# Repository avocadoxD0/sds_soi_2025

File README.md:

# Reaction Wheel Attitude Control System

This repository contains the complete design and development of a single-axis reaction wheel system for satellite attitude stabilization. The project brings together mechanical modeling, circuit design, and embedded control to achieve angular velocity detumbling.

The system is built around a reaction wheel mechanism, controlled using real-time feedback from an onboard IMU. All major subsystems including mechanical structure, electronics, and control algorithm are developed in coordination to function as a unified, self-contained system.

This repository serves as a consolidated record of the entire design process, including CAD models, PCB design files, and control code.

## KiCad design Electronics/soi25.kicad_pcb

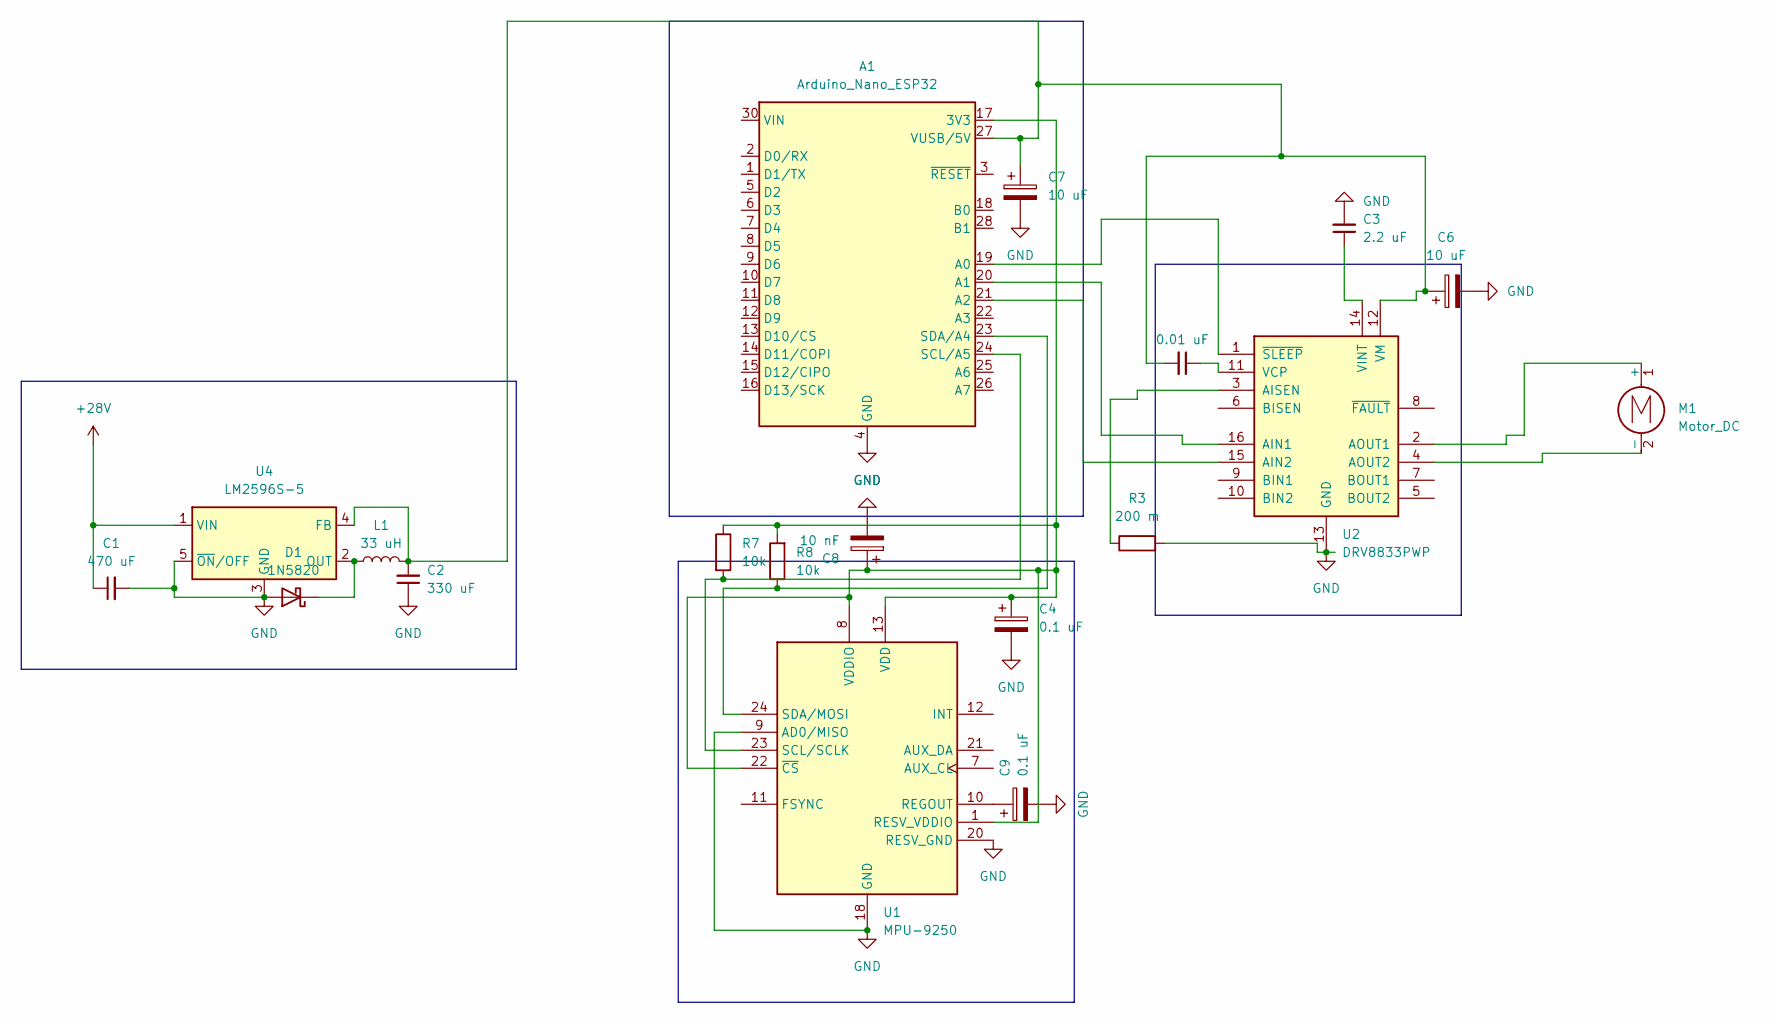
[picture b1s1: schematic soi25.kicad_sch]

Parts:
A1: Arduino_Nano_ESP32; Arduino_Nano
C1: 470 uF; C_Radial_D4.0mm_H5.0mm_P1.50mm
C2: 330 uF; C_Radial_D4.0mm_H5.0mm_P1.50mm
C3: 2.2 uF; C_0402_1005Metric_Pad0.74x0.62mm_HandSolder
C4, C9: 0.1 uF; C_0402_1005Metric_Pad0.74x0.62mm_HandSolder
C5: 0.01 uF; C_0402_1005Metric_Pad0.74x0.62mm_HandSolder
C6, C7: 10 uF; C_0402_1005Metric_Pad0.74x0.62mm_HandSolder
C8: 10 nF; C_0402_1005Metric_Pad0.74x0.62mm_HandSolder
D1: 1N5820; D_0201_0603Metric
L1: 33 uH; L_Wurth_WE-LQSH-2010
M1: Motor_DC; Vybronics_VZ30C1T8219732L
R3: 200 m; R_0402_1005Metric_Pad0.72x0.64mm_HandSolder
R7, R8: 10k; R_0402_1005Metric_Pad0.72x0.64mm_HandSolder
U1: MPU-9250; InvenSense_QFN-24_3x3mm_P0.4mm
U2: DRV8833PWP; HTSSOP-16-1EP_4.4x5mm_P0.65mm_EP3.4x5mm_Mask2.46x2.31mm_The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
U4: LM2596S-5; TO-263-5_TabPin3

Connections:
+28V: C1.1, U4.1 (VIN)
GND: A1.4 (GND), A1.29 (GND), C1.2, C2.1, C3.2, C4.2, C6.2, C7.2, C8.2, C9.2, D1.2 (A), R3.2, U1.9 (AD0/MISO), U1.18 (GND), U1.20 (RESV_GND), U2.13 (GND), U2.17 (GND), U4.3 (GND), U4.5 (~ON/OFF)
unnamed: A1.17 (3V3), C4.1, C8.1, R7.1, R8.2, U1.1 (RESV_VDDIO), U1.8 (VDDIO), U1.13 (VDD), U1.22 (~CS)
unnamed: A1.19 (A0), U2.1 (~SLEEP)
unnamed: A1.20 (A1), U2.16 (AIN1)
unnamed: A1.21 (A2), U2.15 (AIN2)
unnamed: A1.24 (SCL/A5), R7.2, U1.23 (SCL/SCLK)
unnamed: A1.23 (SDA/A4), R8.1, U1.24 (SDA/MOSI)
unnamed: A1.27 (VUSB/5V), C2.2, C5.2, C6.1, C7.1, L1.2, U2.12 (VM), U4.4 (FB)
unnamed: D1.1 (K), L1.1, U4.2 (OUT)
unnamed: M1.1 (+), U2.2 (AOUT1)
unnamed: M1.2 (-), U2.4 (AOUT2)
unnamed: C9.1, U1.10 (REGOUT)
unnamed: R3.1, U2.3 (AISEN)
unnamed: C5.1, U2.11 (VCP)
unnamed: C3.1, U2.14 (VINT)

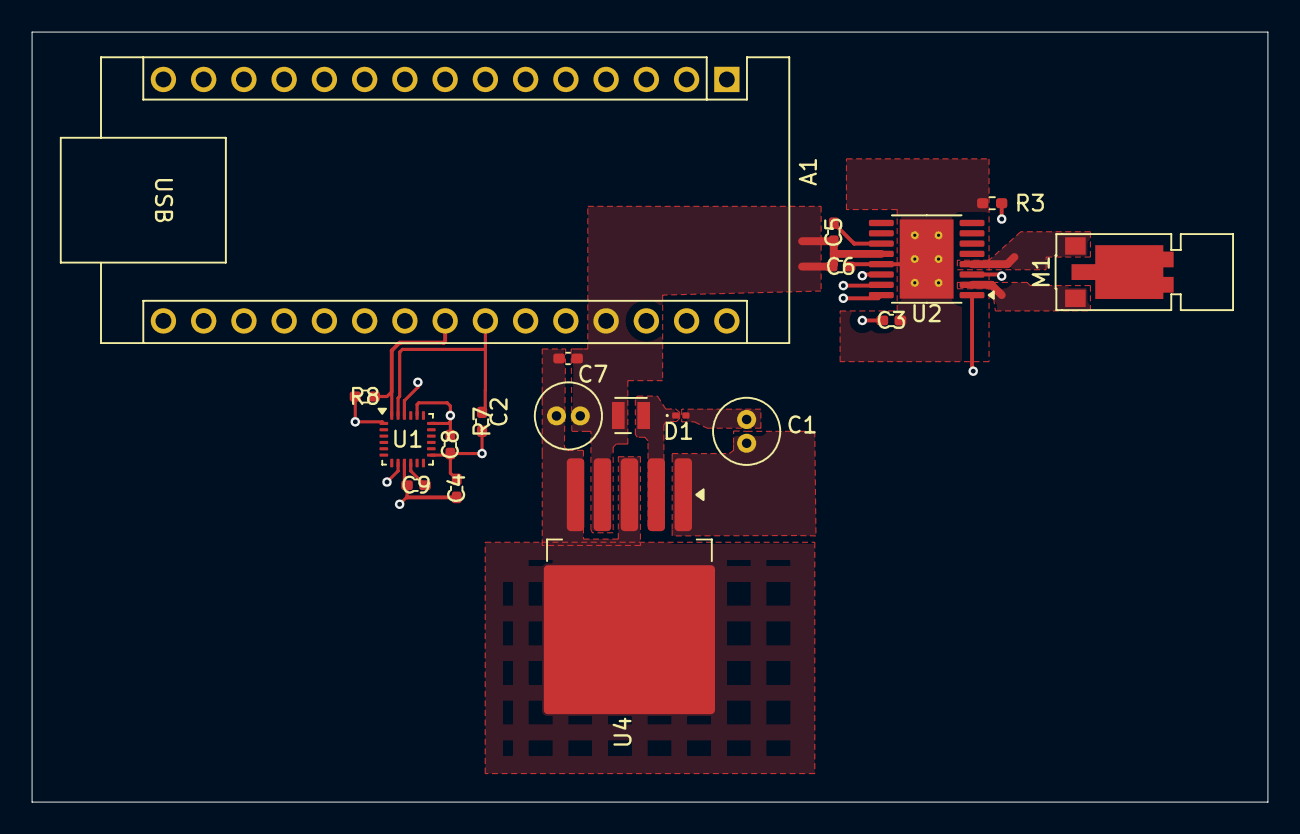
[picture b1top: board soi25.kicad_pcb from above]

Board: 4 copper layers, 78.0 x 48.6 mm, 19 parts (0 on the bottom side), 16 nets.

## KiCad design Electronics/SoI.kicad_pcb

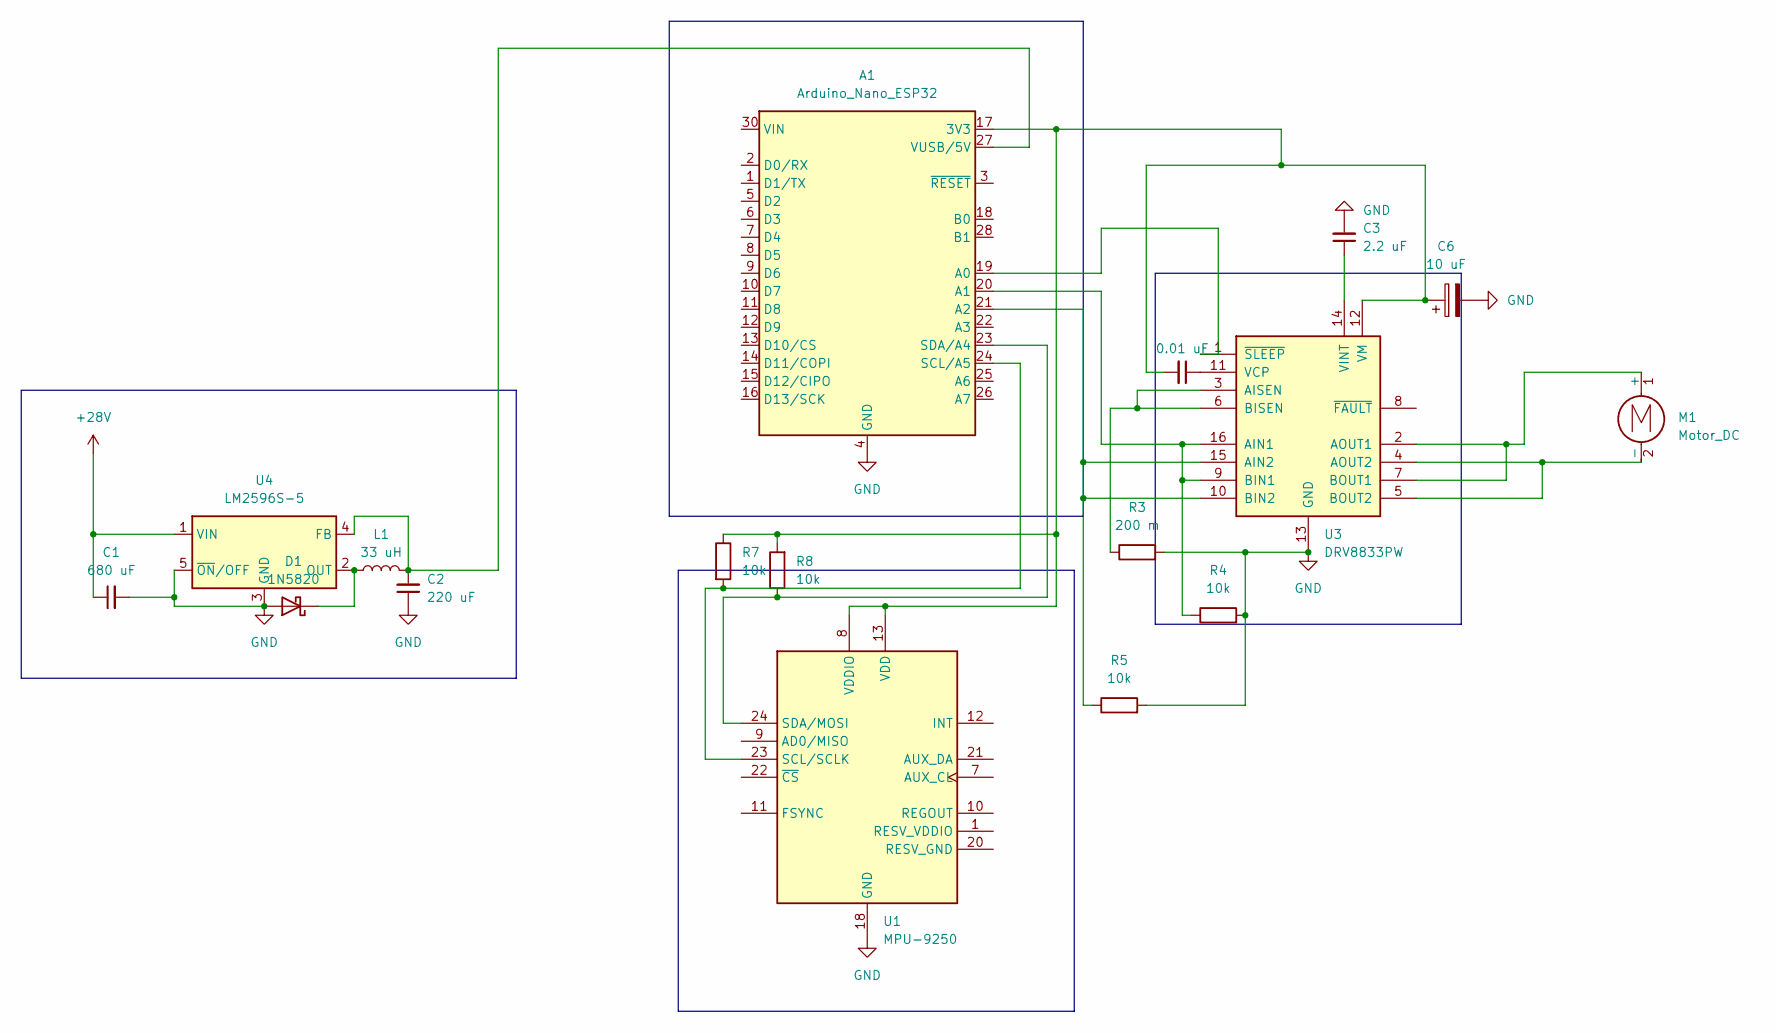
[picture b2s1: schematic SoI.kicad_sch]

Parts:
A1: Arduino_Nano_ESP32; Arduino_Nano
C1: 680 uF; CP_Elec_4x3
C2: 220 uF; CP_Elec_4x3
C3: 2.2 uF; CP_Elec_4x3
C5: 0.01 uF; CP_Elec_4x3
C6: 10 uF; CP_Elec_4x3
D1: 1N5820; D_0201_0603Metric
L1: 33 uH; L_Wurth_WE-LQSH-2010
M1: Motor_DC; Vybronics_VZ30C1T8219732L
R3: 200 m; R_0201_0603Metric
R4, R5, R7, R8: 10k; R_0201_0603Metric
U1: MPU-9250; InvenSense_QFN-24_3x3mm_P0.4mm
U3: DRV8833PW; TSSOP-16_4.4x5mm_P0.65mm
U4: LM2596S-5; TO-263-5_TabPin3

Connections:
+28V: C1.1, U4.1 (VIN)
GND: A1.4 (GND), A1.29 (GND), C1.2, C2.1, C3.2, C6.2, D1.2 (A), R3.2, R4.2, R5.2, U1.18 (GND), U3.13 (GND), U4.3 (GND), U4.5 (~ON/OFF)
unnamed: A1.17 (3V3), C5.2, C6.1, R7.1, R8.2, U1.8 (VDDIO), U1.13 (VDD), U3.12 (VM)
unnamed: A1.19 (A0), U3.1 (~SLEEP)
unnamed: A1.20 (A1), R4.1, U3.9 (BIN1), U3.16 (AIN1)
unnamed: A1.21 (A2), R5.1, U3.10 (BIN2), U3.15 (AIN2)
unnamed: A1.24 (SCL/A5), R7.2, U1.23 (SCL/SCLK)
unnamed: A1.23 (SDA/A4), R8.1, U1.24 (SDA/MOSI)
unnamed: A1.27 (VUSB/5V), C2.2, L1.2, U4.4 (FB)
unnamed: D1.1 (K), L1.1, U4.2 (OUT)
unnamed: M1.1 (+), U3.2 (AOUT1), U3.7 (BOUT1)
unnamed: M1.2 (-), U3.4 (AOUT2), U3.5 (BOUT2)
unnamed: R3.1, U3.3 (AISEN), U3.6 (BISEN)
unnamed: C5.1, U3.11 (VCP)
unnamed: C3.1, U3.14 (VINT)

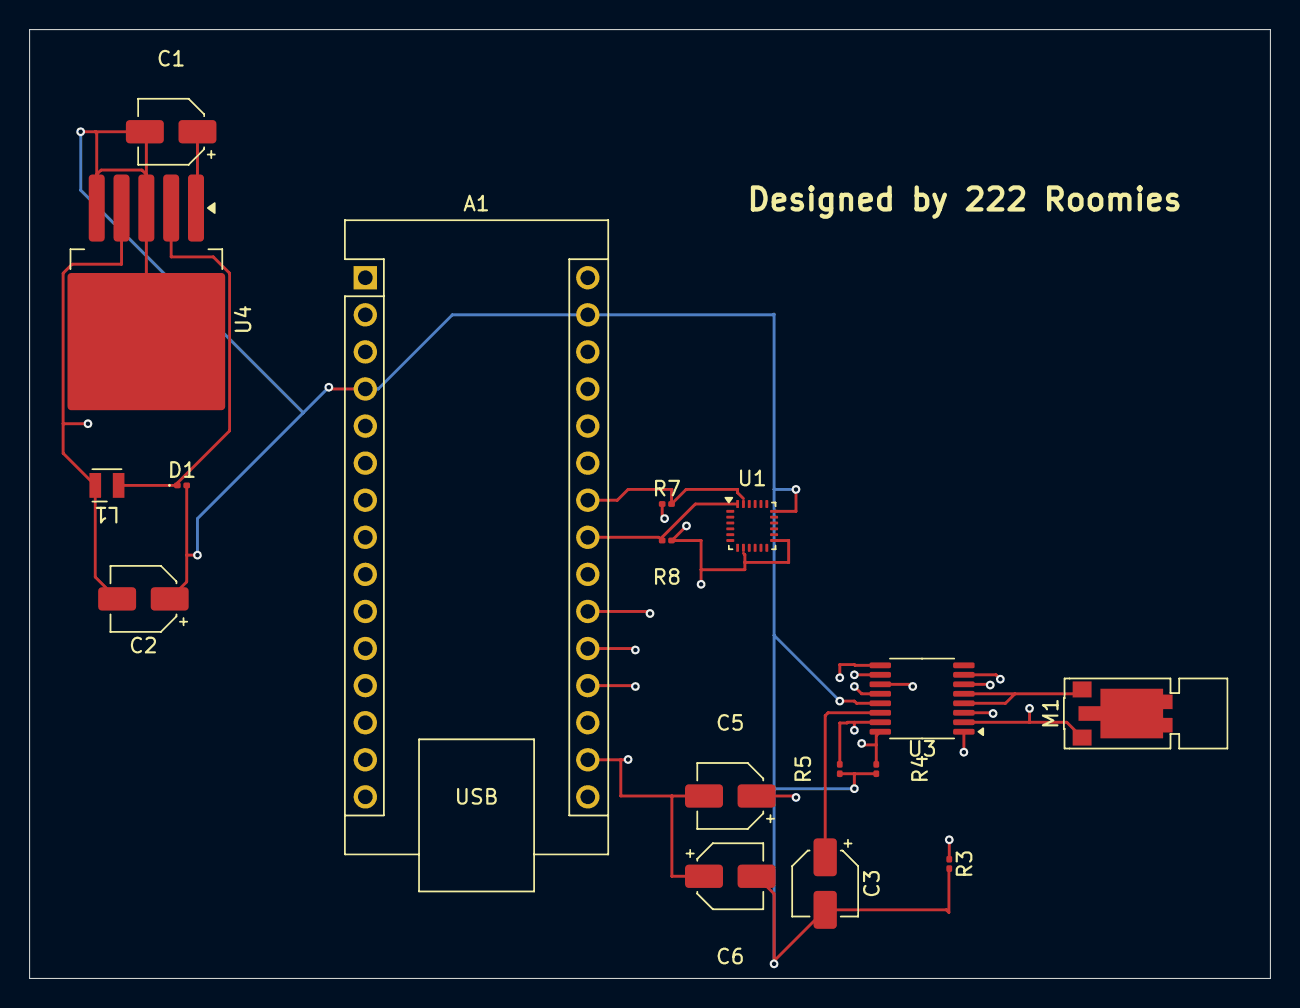
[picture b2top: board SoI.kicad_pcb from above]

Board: 4 copper layers, 85.0 x 65.0 mm, 17 parts (0 on the bottom side), 15 nets.

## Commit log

2025-07-04 CAD/Solidworks_src/
2025-07-04 Create temp
2025-07-04 Create temp1
2025-07-04 Create temp2
2025-07-11 Schematic and PCB files
2025-07-11 PCB Explanation PDF
2025-07-14 Update the pcb and schematic
2025-07-14 Delete Electronics/pcb_design_document.pdf
    New version coming up
2025-07-14 New doc getting added
